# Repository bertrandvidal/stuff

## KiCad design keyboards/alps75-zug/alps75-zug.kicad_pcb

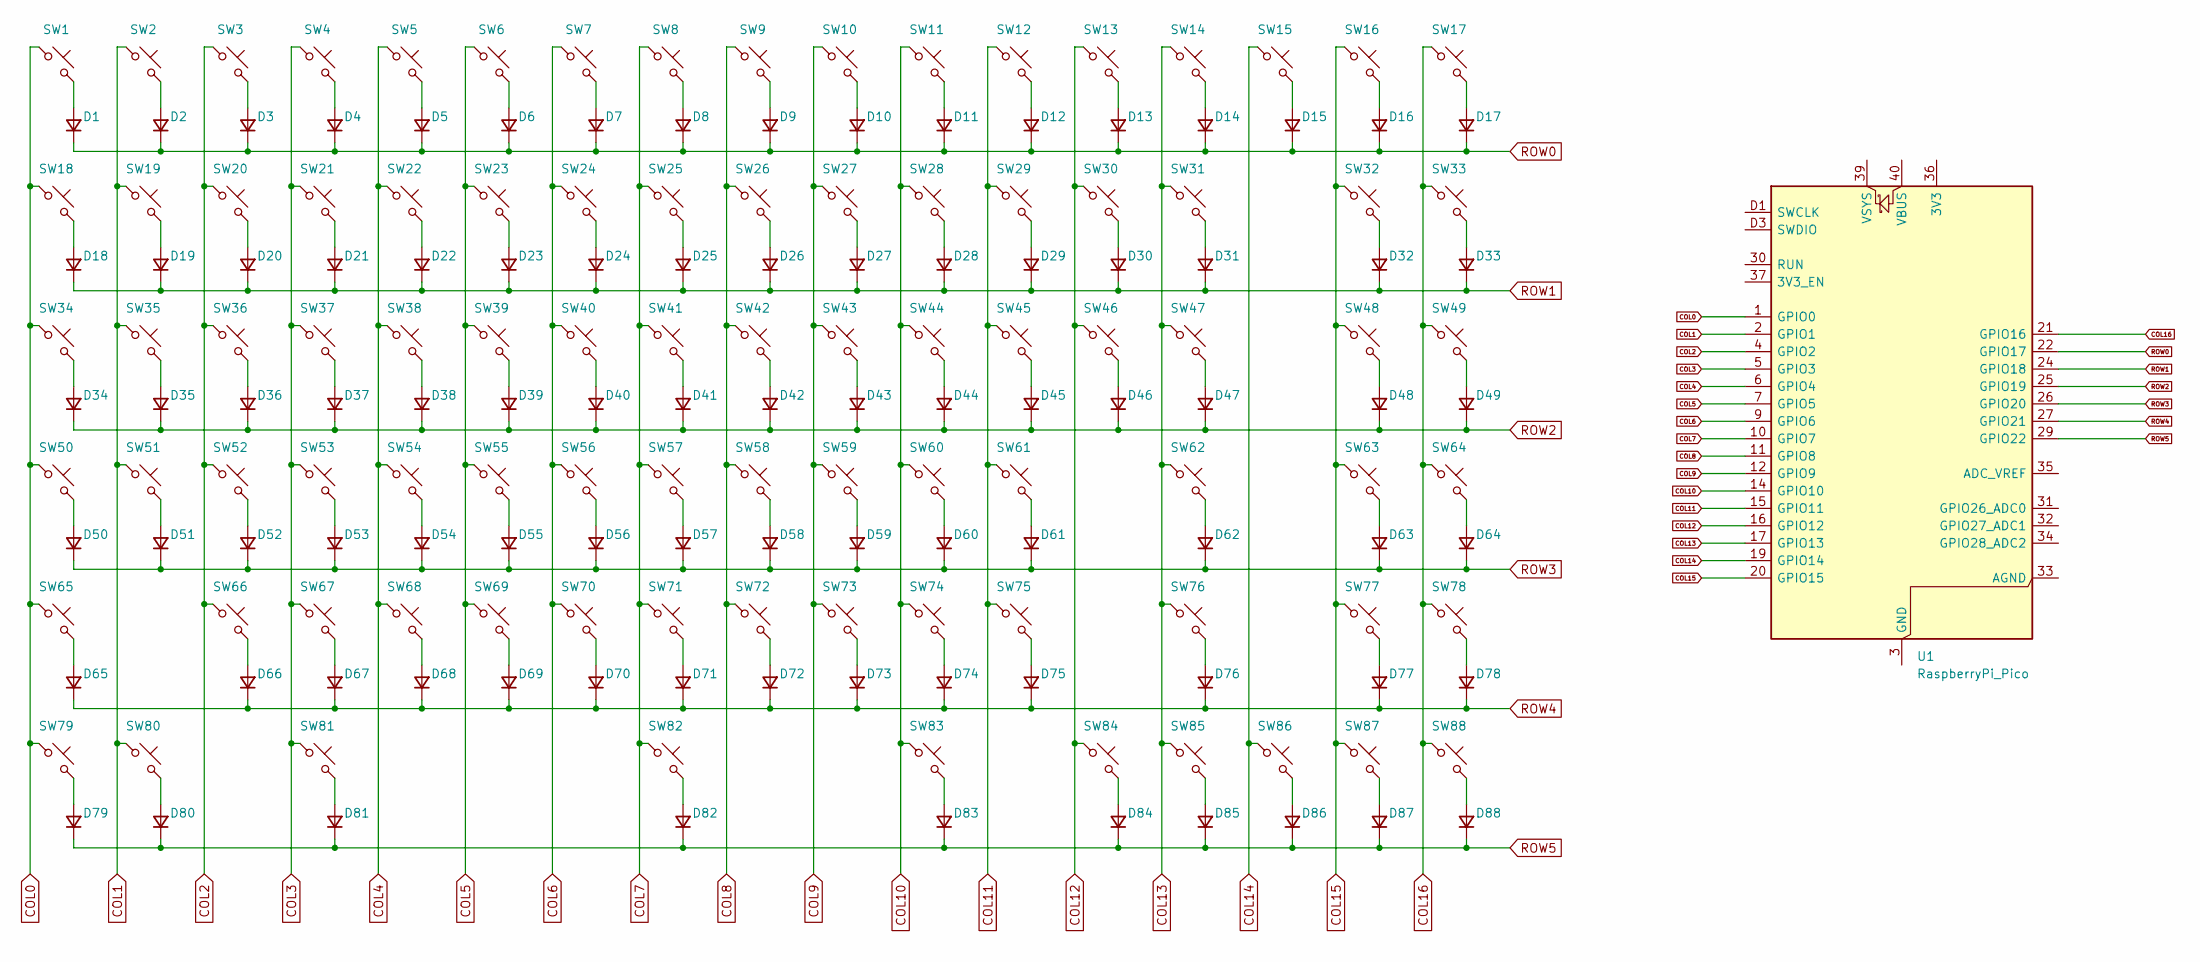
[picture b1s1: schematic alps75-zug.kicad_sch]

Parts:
D1, D2, D3, D4, D5, D6, D7, D8, D9, D10, D11, D12, D13, D14, D15, D16, D17, D18, D19, D20, D21, D22, D23, D24, D25, D26, D27, D28, D29, D30, D31, D32, D33, D34, D35, D36, D37, D38, D39, D40, D41, D42, D43, D44, D45, D46, D47, D48, D49, D50, D51, D52, D53, D54, D55, D56, D57, D58, D59, D60, D61, D62, D63, D64, D65, D66, D67, D68, D69, D70, D71, D72, D73, D74, D75, D76, D77, D78, D79, D80, D81, D82, D83, D84, D85, D86, D87, D88: 1N4148WL; D_SOD-123F; LCSC C108804
SW1, SW2, SW3, SW4, SW5, SW6, SW7, SW8, SW9, SW10, SW11, SW12, SW13, SW14, SW15, SW16, SW17, SW18, SW19, SW20, SW21, SW22, SW23, SW24, SW25, SW26, SW27, SW28, SW29, SW30, SW32, SW33, SW35, SW36, SW37, SW38, SW39, SW40, SW41, SW42, SW43, SW44, SW45, SW46, SW48, SW49, SW51, SW52, SW53, SW54, SW55, SW56, SW57, SW58, SW59, SW60, SW61, SW63, SW64, SW66, SW67, SW68, SW69, SW70, SW71, SW72, SW73, SW74, SW75, SW77, SW78, SW84, SW85, SW86, SW87, SW88: SW_Push; SW_Alps_Matias_1.00u
SW31: SW_Push; SW_Alps_Matias_2.00u
SW34, SW47, SW79, SW81: SW_Push; SW_Alps_Matias_1.50u
SW50: SW_Push; SW_Alps_Matias_1.75u
SW62, SW65: SW_Push; SW_Alps_Matias_2.25u
SW76: SW_Push; SW_Alps_Matias_2.75u
SW80, SW83: SW_Push; SW_Alps_Matias_1.25u
SW82: SW_Push; SW_Alps_Matias_6.50u
U1: RaspberryPi_Pico; RaspberryPi_Pico_SMD_HandSolder

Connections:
COL0: SW1.1, SW18.1, SW34.1, SW50.1, SW65.1, SW79.1, U1.1 (GPIO0)
COL1: SW2.1, SW19.1, SW35.1, SW51.1, SW80.1, U1.2 (GPIO1)
COL2: SW3.1, SW20.1, SW36.1, SW52.1, SW66.1, U1.4 (GPIO2)
COL3: SW4.1, SW21.1, SW37.1, SW53.1, SW67.1, SW81.1, U1.5 (GPIO3)
COL4: SW5.1, SW22.1, SW38.1, SW54.1, SW68.1, U1.6 (GPIO4)
COL5: SW6.1, SW23.1, SW39.1, SW55.1, SW69.1, U1.7 (GPIO5)
COL6: SW7.1, SW24.1, SW40.1, SW56.1, SW70.1, U1.9 (GPIO6)
COL7: SW8.1, SW25.1, SW41.1, SW57.1, SW71.1, SW82.1, U1.10 (GPIO7)
COL8: SW9.1, SW26.1, SW42.1, SW58.1, SW72.1, U1.11 (GPIO8)
COL9: SW10.1, SW27.1, SW43.1, SW59.1, SW73.1, U1.12 (GPIO9)
COL10: SW11.1, SW28.1, SW44.1, SW60.1, SW74.1, SW83.1, U1.14 (GPIO10)
COL11: SW12.1, SW29.1, SW45.1, SW61.1, SW75.1, U1.15 (GPIO11)
COL12: SW13.1, SW30.1, SW46.1, SW84.1, U1.16 (GPIO12)
COL13: SW14.1, SW31.1, SW47.1, SW62.1, SW76.1, SW85.1, U1.17 (GPIO13)
COL14: SW15.1, SW86.1, U1.19 (GPIO14)
COL15: SW16.1, SW32.1, SW48.1, SW63.1, SW77.1, SW87.1, U1.20 (GPIO15)
COL16: SW17.1, SW33.1, SW49.1, SW64.1, SW78.1, SW88.1, U1.21 (GPIO16)
unnamed: D1.2 (A), SW1.2
unnamed: D2.2 (A), SW2.2
unnamed: D3.2 (A), SW3.2
unnamed: D4.2 (A), SW4.2
unnamed: D5.2 (A), SW5.2
unnamed: D6.2 (A), SW6.2
unnamed: D7.2 (A), SW7.2
unnamed: D8.2 (A), SW8.2
unnamed: D9.2 (A), SW9.2
unnamed: D10.2 (A), SW10.2
unnamed: D11.2 (A), SW11.2
unnamed: D12.2 (A), SW12.2
unnamed: D13.2 (A), SW13.2
unnamed: D14.2 (A), SW14.2
unnamed: D15.2 (A), SW15.2
unnamed: D16.2 (A), SW16.2
unnamed: D17.2 (A), SW17.2
unnamed: D18.2 (A), SW18.2
unnamed: D19.2 (A), SW19.2
unnamed: D20.2 (A), SW20.2
unnamed: D21.2 (A), SW21.2
unnamed: D22.2 (A), SW22.2
unnamed: D23.2 (A), SW23.2
unnamed: D24.2 (A), SW24.2
unnamed: D25.2 (A), SW25.2
unnamed: D26.2 (A), SW26.2
unnamed: D27.2 (A), SW27.2
unnamed: D28.2 (A), SW28.2
unnamed: D29.2 (A), SW29.2
unnamed: D30.2 (A), SW30.2
unnamed: D31.2 (A), SW31.2
unnamed: D32.2 (A), SW32.2
unnamed: D33.2 (A), SW33.2
unnamed: D34.2 (A), SW34.2
unnamed: D35.2 (A), SW35.2
unnamed: D36.2 (A), SW36.2
unnamed: D37.2 (A), SW37.2
unnamed: D38.2 (A), SW38.2
unnamed: D39.2 (A), SW39.2
unnamed: D40.2 (A), SW40.2
unnamed: D41.2 (A), SW41.2
unnamed: D42.2 (A), SW42.2
unnamed: D43.2 (A), SW43.2
unnamed: D44.2 (A), SW44.2
unnamed: D45.2 (A), SW45.2
unnamed: D46.2 (A), SW46.2
unnamed: D47.2 (A), SW47.2
unnamed: D48.2 (A), SW48.2
unnamed: D49.2 (A), SW49.2
unnamed: D50.2 (A), SW50.2
unnamed: D51.2 (A), SW51.2
unnamed: D52.2 (A), SW52.2
unnamed: D53.2 (A), SW53.2
unnamed: D54.2 (A), SW54.2
unnamed: D55.2 (A), SW55.2
unnamed: D56.2 (A), SW56.2
unnamed: D57.2 (A), SW57.2
unnamed: D58.2 (A), SW58.2
unnamed: D59.2 (A), SW59.2
unnamed: D60.2 (A), SW60.2
unnamed: D61.2 (A), SW61.2
unnamed: D62.2 (A), SW62.2
unnamed: D63.2 (A), SW63.2
unnamed: D64.2 (A), SW64.2
unnamed: D65.2 (A), SW65.2
unnamed: D66.2 (A), SW66.2
unnamed: D67.2 (A), SW67.2
unnamed: D68.2 (A), SW68.2
unnamed: D69.2 (A), SW69.2
unnamed: D70.2 (A), SW70.2
unnamed: D71.2 (A), SW71.2
unnamed: D72.2 (A), SW72.2
unnamed: D73.2 (A), SW73.2
unnamed: D74.2 (A), SW74.2
unnamed: D75.2 (A), SW75.2
unnamed: D76.2 (A), SW76.2
unnamed: D77.2 (A), SW77.2
unnamed: D78.2 (A), SW78.2
unnamed: D79.2 (A), SW79.2
unnamed: D80.2 (A), SW80.2
unnamed: D81.2 (A), SW81.2
unnamed: D82.2 (A), SW82.2
unnamed: D83.2 (A), SW83.2
unnamed: D84.2 (A), SW84.2
unnamed: D85.2 (A), SW85.2
unnamed: D86.2 (A), SW86.2
unnamed: D87.2 (A), SW87.2
unnamed: D88.2 (A), SW88.2
unnamed: U1.3 (GND), U1.8 (GND), U1.13 (GND), U1.18 (GND), U1.23 (GND), U1.28 (GND), U1.38 (GND), U1.D2 (GND)
ROW0: D1.1 (K), D2.1 (K), D3.1 (K), D4.1 (K), D5.1 (K), D6.1 (K), D7.1 (K), D8.1 (K), D9.1 (K), D10.1 (K), D11.1 (K), D12.1 (K), D13.1 (K), D14.1 (K), D15.1 (K), D16.1 (K), D17.1 (K), U1.22 (GPIO17)
ROW1: D18.1 (K), D19.1 (K), D20.1 (K), D21.1 (K), D22.1 (K), D23.1 (K), D24.1 (K), D25.1 (K), D26.1 (K), D27.1 (K), D28.1 (K), D29.1 (K), D30.1 (K), D31.1 (K), D32.1 (K), D33.1 (K), U1.24 (GPIO18)
ROW2: D34.1 (K), D35.1 (K), D36.1 (K), D37.1 (K), D38.1 (K), D39.1 (K), D40.1 (K), D41.1 (K), D42.1 (K), D43.1 (K), D44.1 (K), D45.1 (K), D46.1 (K), D47.1 (K), D48.1 (K), D49.1 (K), U1.25 (GPIO19)
ROW3: D50.1 (K), D51.1 (K), D52.1 (K), D53.1 (K), D54.1 (K), D55.1 (K), D56.1 (K), D57.1 (K), D58.1 (K), D59.1 (K), D60.1 (K), D61.1 (K), D62.1 (K), D63.1 (K), D64.1 (K), U1.26 (GPIO20)
ROW4: D65.1 (K), D66.1 (K), D67.1 (K), D68.1 (K), D69.1 (K), D70.1 (K), D71.1 (K), D72.1 (K), D73.1 (K), D74.1 (K), D75.1 (K), D76.1 (K), D77.1 (K), D78.1 (K), U1.27 (GPIO21)
ROW5: D79.1 (K), D80.1 (K), D81.1 (K), D82.1 (K), D83.1 (K), D84.1 (K), D85.1 (K), D86.1 (K), D87.1 (K), D88.1 (K), U1.29 (GPIO22)

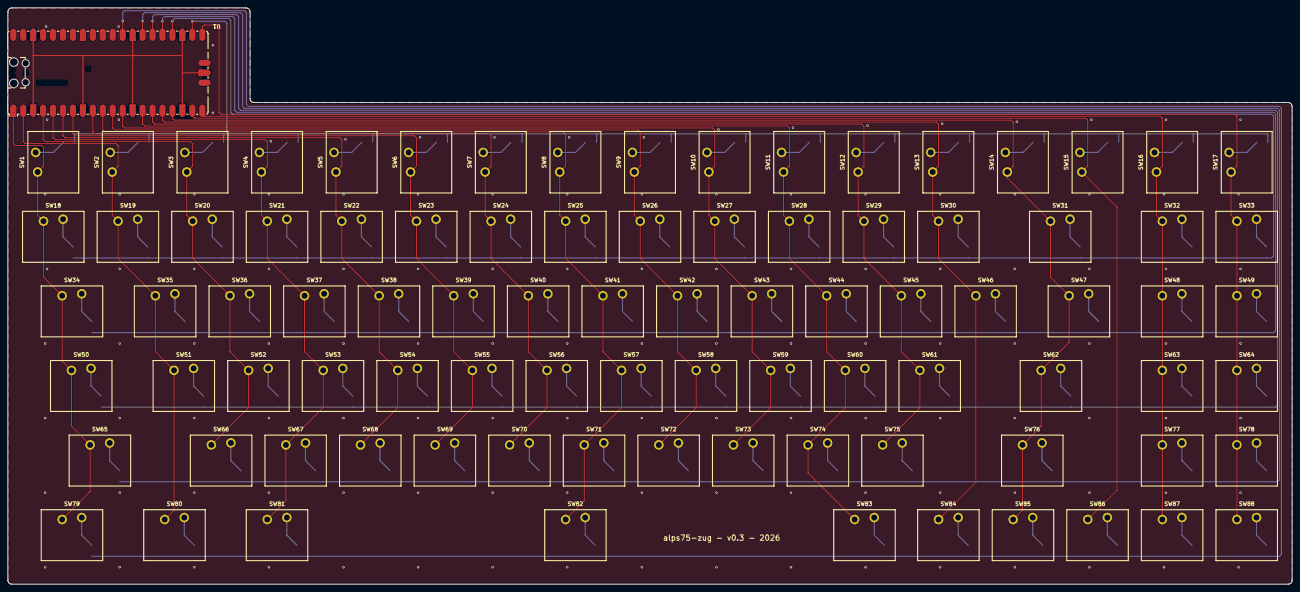
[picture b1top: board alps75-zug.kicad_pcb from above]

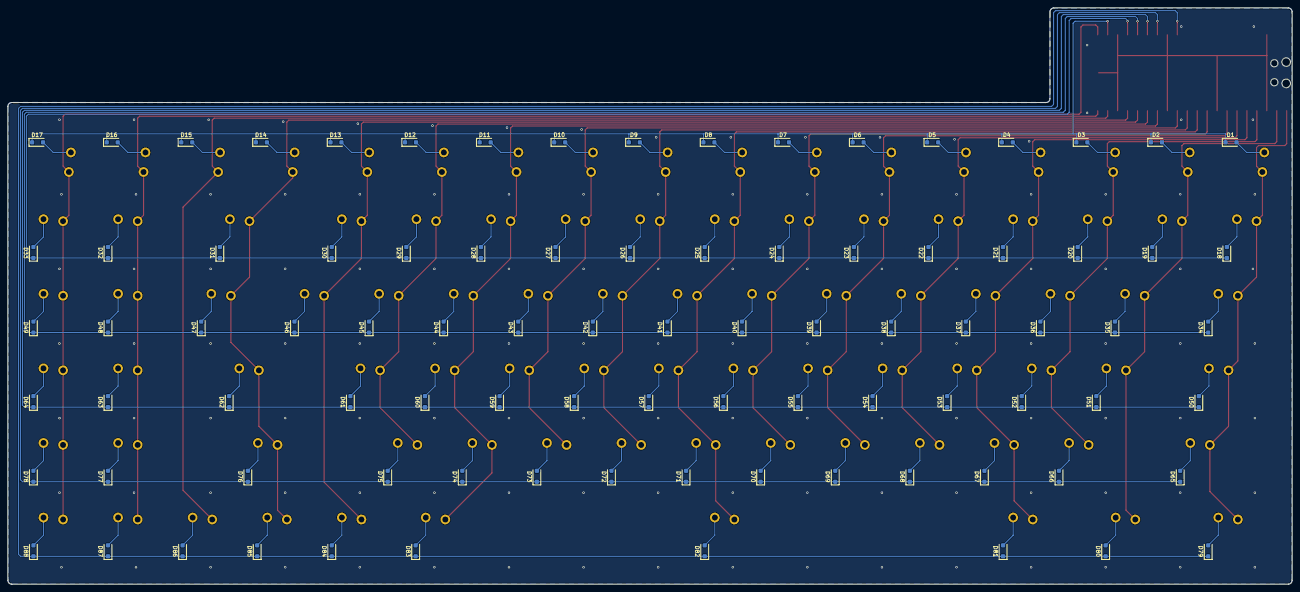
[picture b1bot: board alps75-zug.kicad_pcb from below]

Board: 2 copper layers, 328.0 x 147.2 mm, 177 parts (88 on the bottom side), 112 nets.

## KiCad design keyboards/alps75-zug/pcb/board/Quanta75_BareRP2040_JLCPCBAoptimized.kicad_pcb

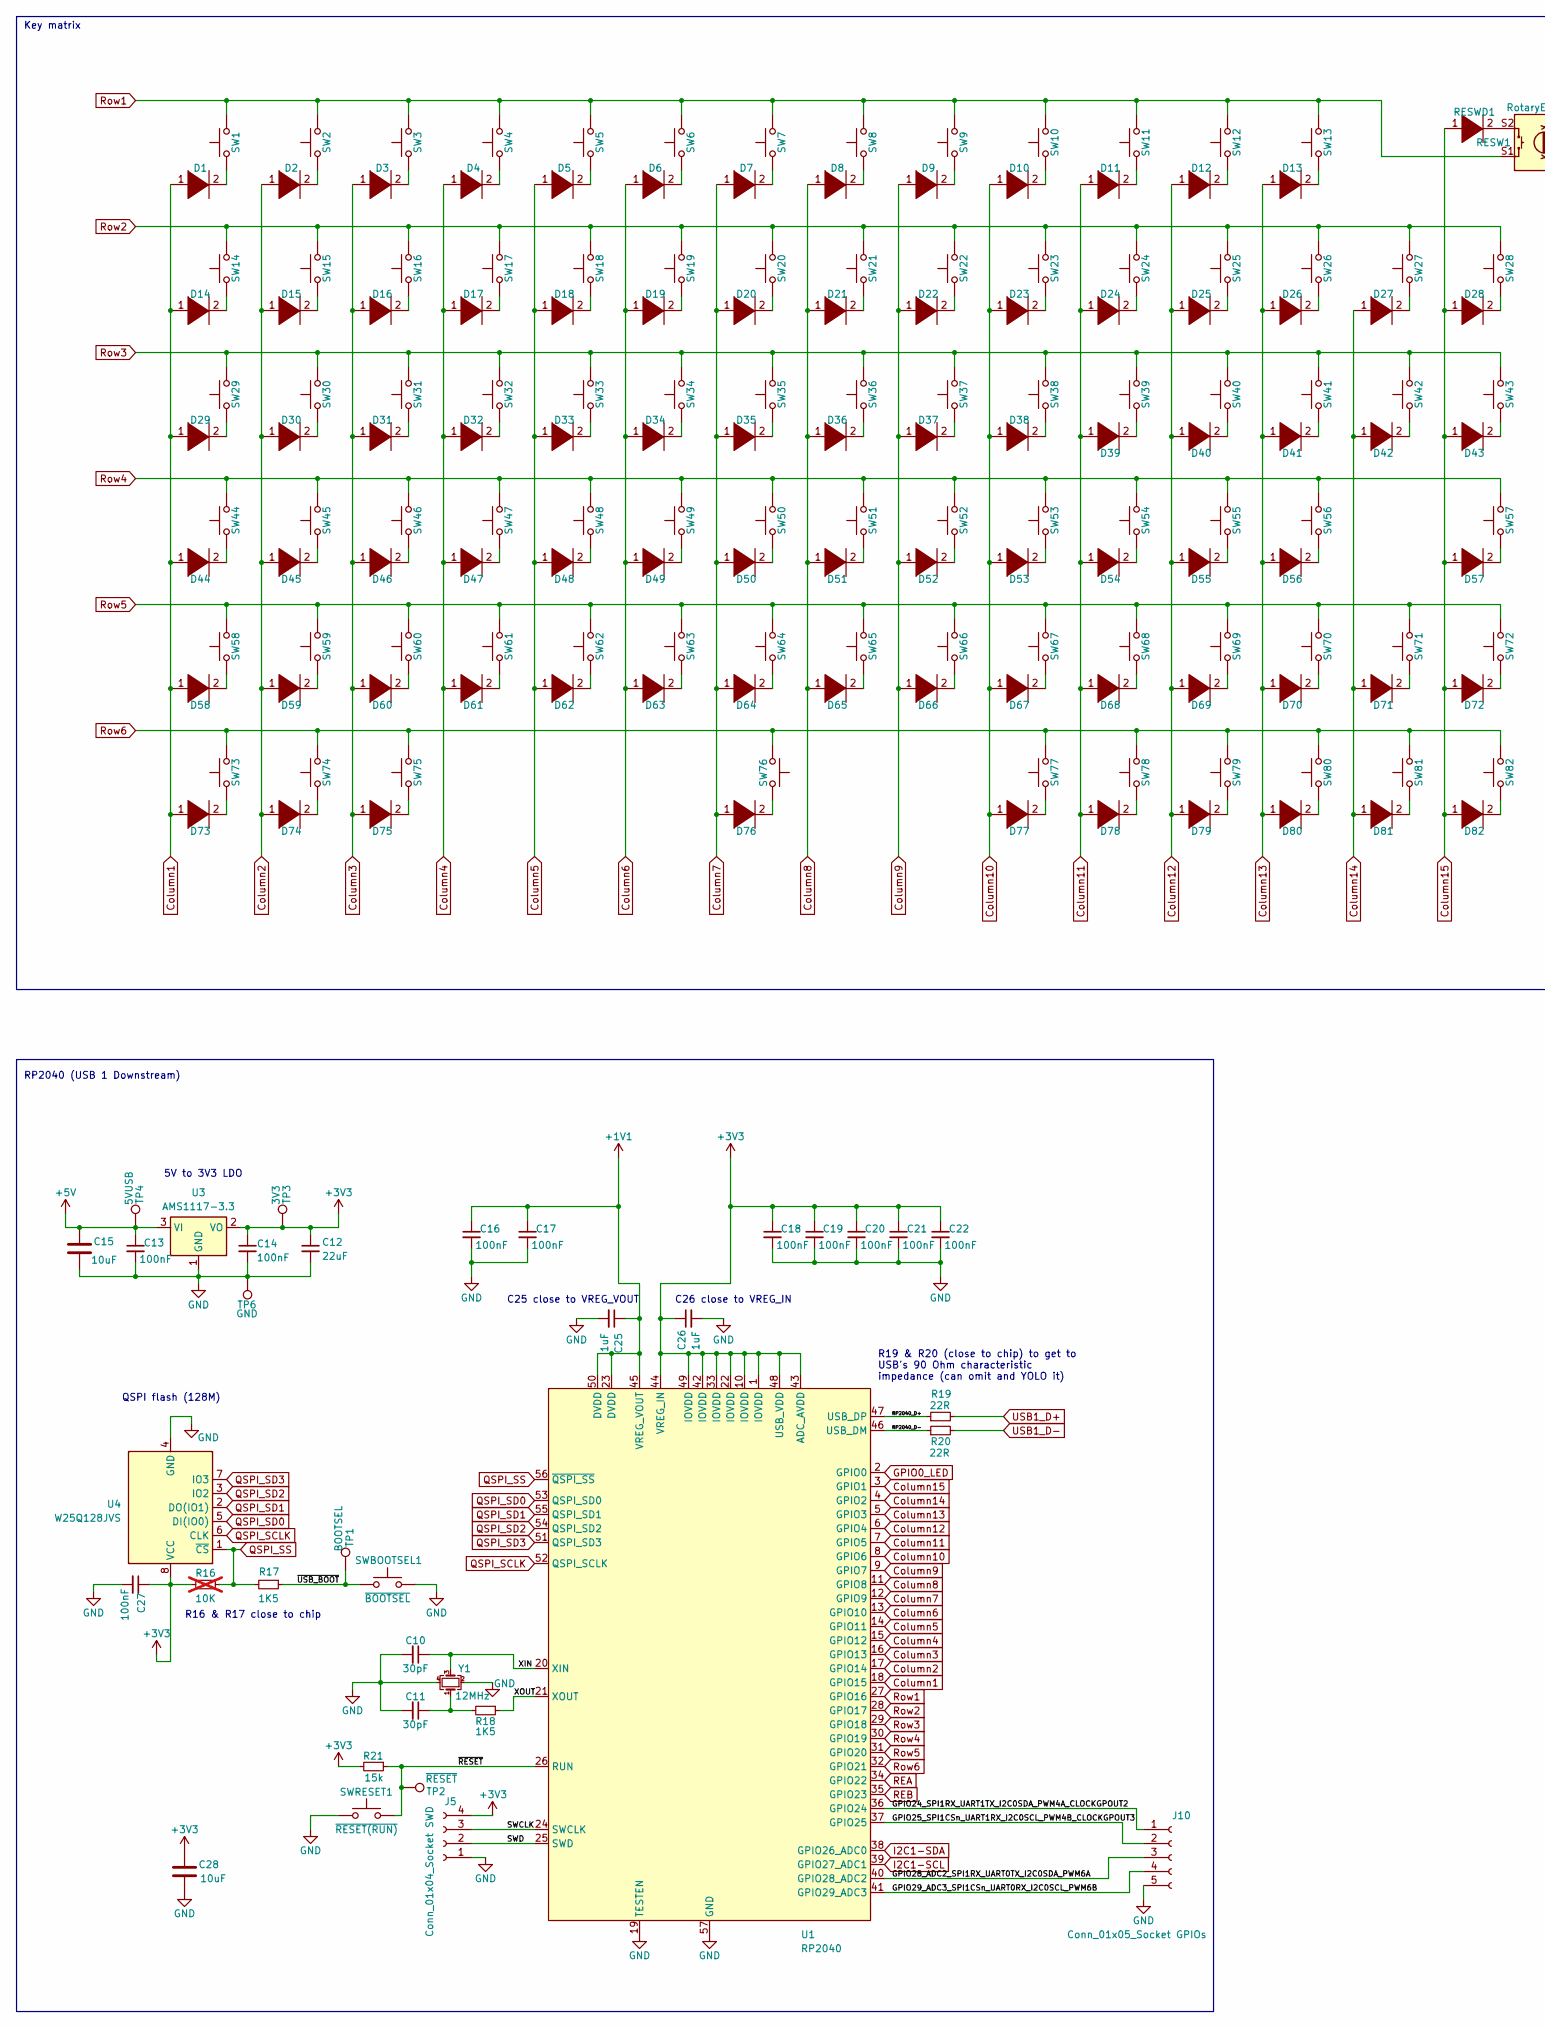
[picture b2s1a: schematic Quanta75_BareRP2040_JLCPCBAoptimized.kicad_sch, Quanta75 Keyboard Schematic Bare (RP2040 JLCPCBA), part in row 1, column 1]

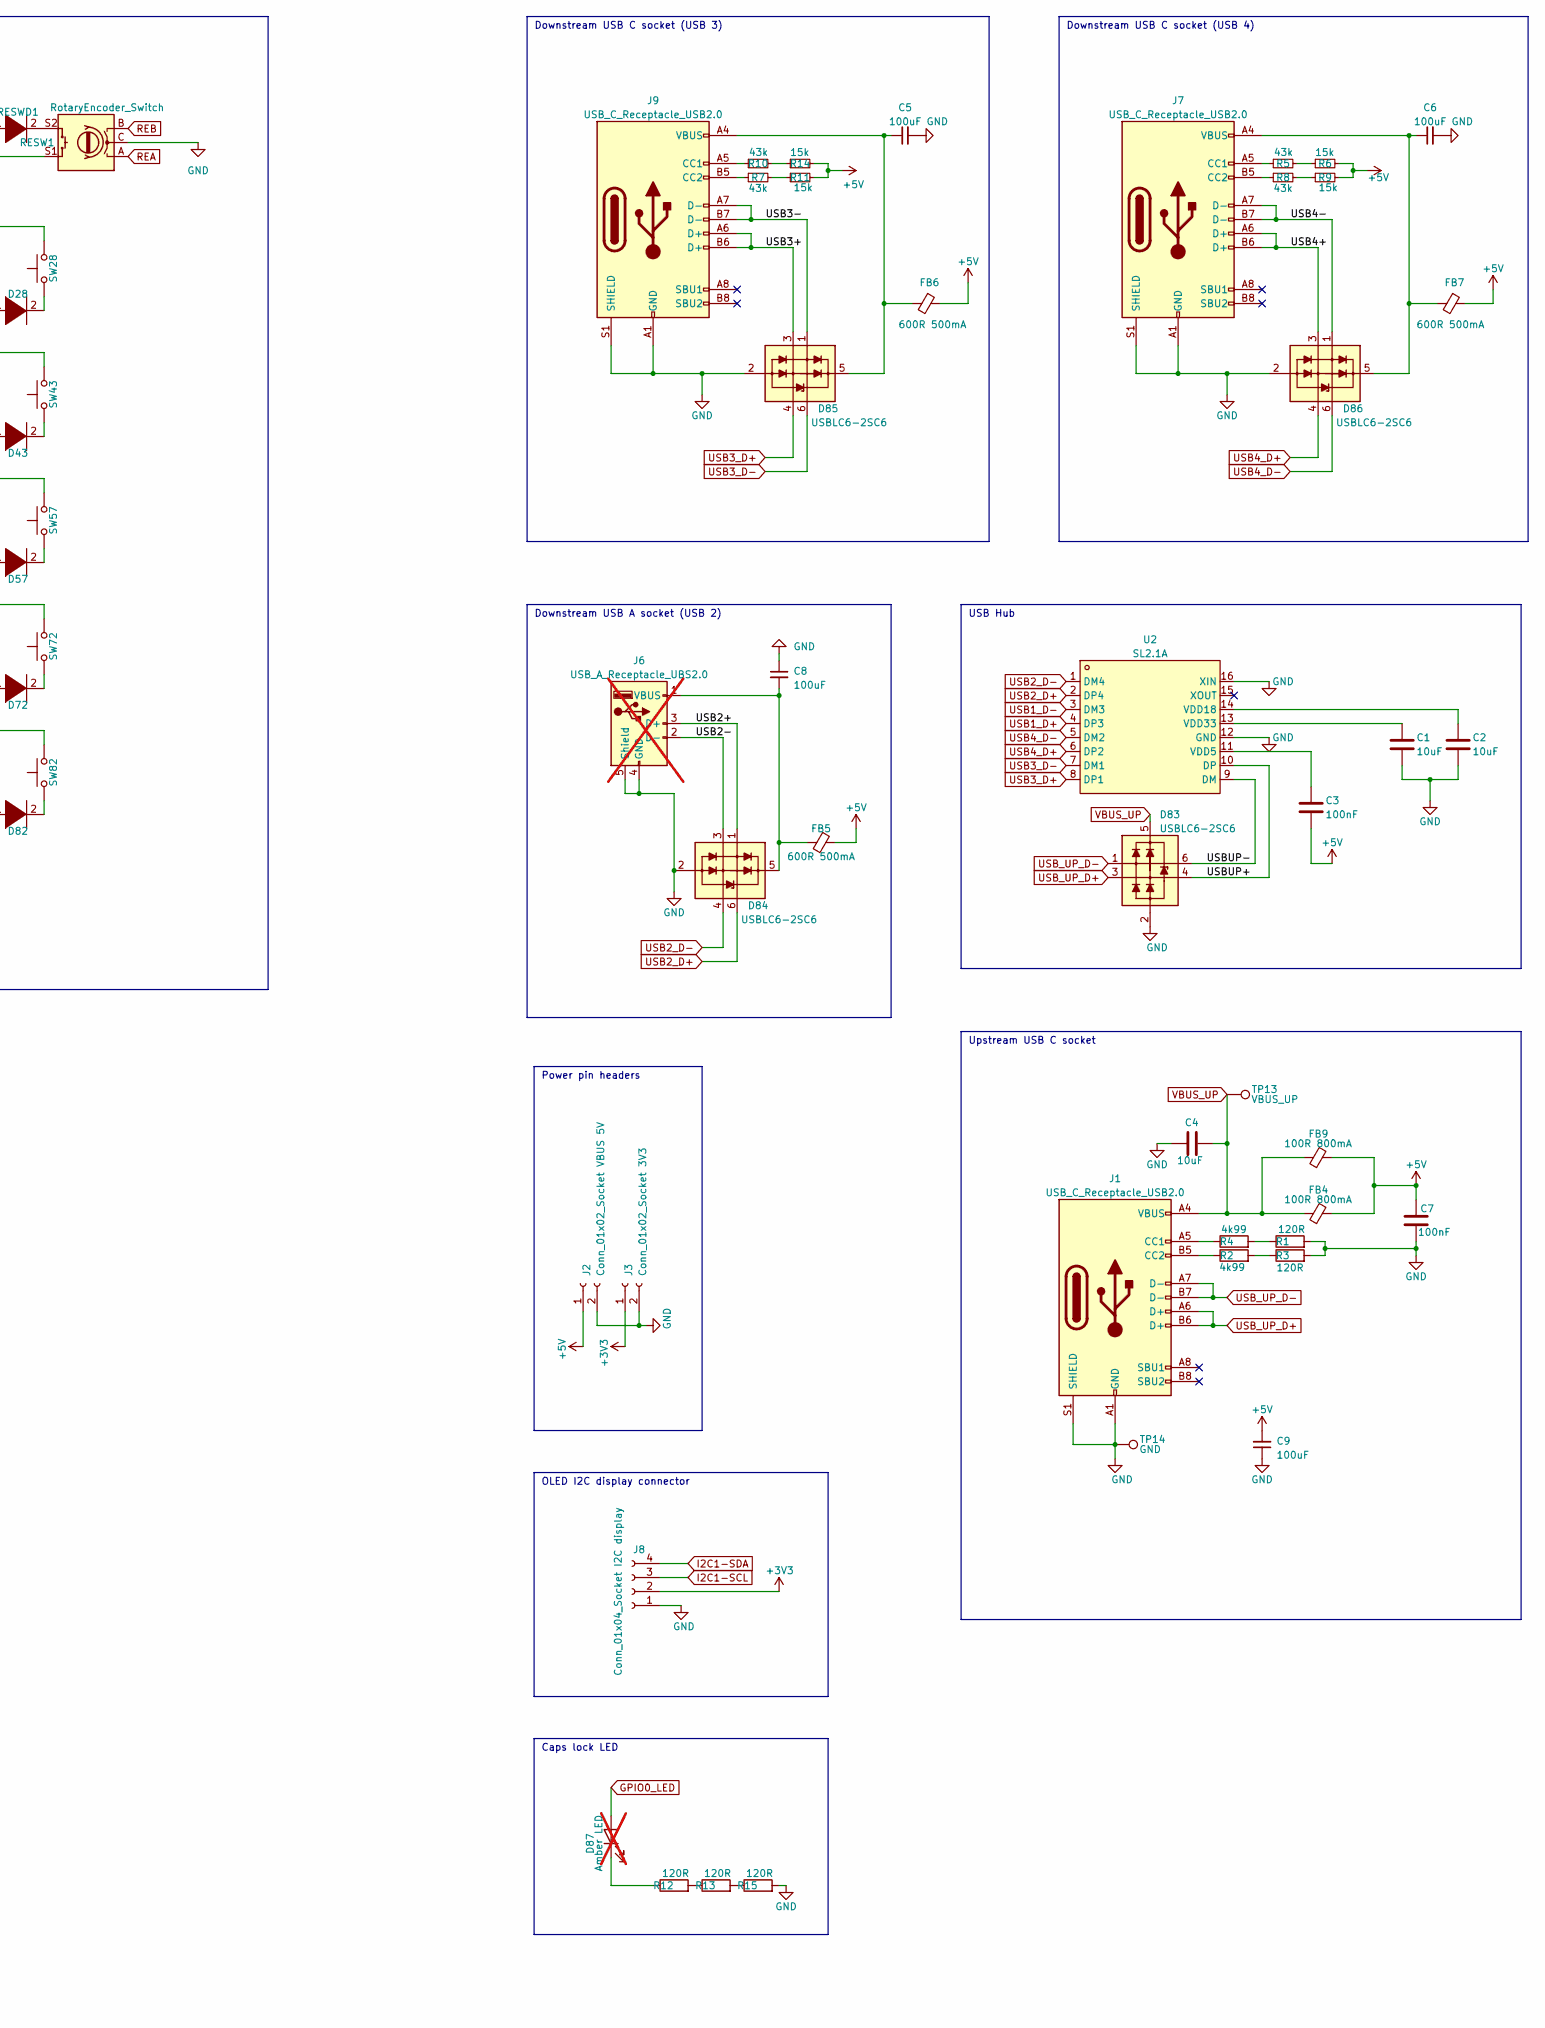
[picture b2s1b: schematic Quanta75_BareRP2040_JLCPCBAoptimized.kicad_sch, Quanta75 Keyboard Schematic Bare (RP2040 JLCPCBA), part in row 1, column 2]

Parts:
C1, C2, C4, C15, C28: 10uF; C_0603_1608Metric_Pad1.08x0.95mm_HandSolder; JLCPCB C96446
C3, C7, C13, C14, C16, C17, C18, C19, C20, C21, C22: 100nF; C_0603_1608Metric_Pad1.08x0.95mm_HandSolder; JLCPCB C14663
C5, C6, C8, C9: 100uF; C_1206_3216Metric_Pad1.33x1.80mm_HandSolder; JLCPCB C15008
C10, C11: 30pF; C_0603_1608Metric_Pad1.08x0.95mm_HandSolder; JLCPCB C1658
C12: 22uF; C_0805_2012Metric_Pad1.18x1.45mm_HandSolder; JLCPCB C45783
C25, C26: 1uF; C_0402_1005Metric_Pad0.74x0.62mm_HandSolder; JLCPCB C52923
C27: 100nF; R_0603_1608Metric_Pad0.98x0.95mm_HandSolder; JLCPCB C14663
D1: DIODE; D_SOD-123; JLCPCB C81598
D2, D3, D4, D5, D6, D7, D8, D9, D10, D11, D12, D13, D14, D15, D16, D17, D18, D19, D20, D21, D22, D23, D24, D25, D26, D27, D28, D29, D30, D31, D32, D33, D34, D35, D36, D37, D38, D39, D40, D41, D42, D43, D44, D45, D46, D47, D48, D49, D50, D51, D52, D53, D54, D55, D56, D57, D58, D59, D60, D61, D62, D63, D64, D65, D66, D67, D68, D69, D70, D71, D72, D73, D74, D75, D76, D77, D78, D79, D80, D81, D82: DIODE; D_SOD-123
D83, D84, D85, D86: USBLC6-2SC6; SOT-23-6_Handsoldering
D87: Amber LED; LED_D5.0mm_Clear; not fitted
FB4, FB9: 100R 800mA; Ferrite_0805_2012Metric_Pad1.05x1.20mm_BigPads; JLCPCB part number C1015
FB5: 600R 500mA; Ferrite_0805_2012Metric; JLCPCB part number C1017
FB6, FB7: 600R 500mA; Ferrite_0805_2012Metric; JLCPCB part numb C1017
J1, J7, J9: USB_C_Receptacle_USB2.0; USB-C-SMD_G-SWITCH_GT-USB-7010EN; JLCPCB C3001293
J2: Conn_01x02_Socket VBUS 5V; PinHeader_1x02_P2.54mm_Vertical
J3: Conn_01x02_Socket 3V3; PinHeader_1x02_P2.54mm_Vertical
J5: Conn_01x04_Socket SWD; PinHeader_1x04_P2.54mm_Vertical
J6: USB_A_Receptacle_UBS2.0; USB-A-TH_KH-AF180ZJ-13.7; JLCPCB C2833345; not fitted
J8: Conn_01x04_Socket I2C display; PinHeader_1x04_P2.54mm_Vertical
J10: Conn_01x05_Socket GPIOs; PinHeader_1x05_P2.54mm_Vertical
R1, R3, R12, R13, R15: 120R; R_0603_1608Metric_Pad0.98x0.95mm_HandSolder; JLCPCB C22787
R2, R4: 4k99; R_0603_1608Metric_Pad0.98x0.95mm_HandSolder; JLCPCB C23046
R5, R7, R8, R10: 43k; R_0603_1608Metric_Pad0.98x0.95mm_HandSolder; JLCPCB C23172
R6, R9, R11, R14, R21: 15k; R_0603_1608Metric_Pad0.98x0.95mm_HandSolder; JLCPCB C22809
R16: 10K; R_0603_1608Metric_Pad0.98x0.95mm_HandSolder; not fitted
R17, R18: 1K5; R_0603_1608Metric_Pad0.98x0.95mm_HandSolder; JLCPCB C22843
R19, R20: 22R; R_0402_1005Metric_Pad0.72x0.64mm_HandSolder; JLCPCB C25092
RESW1: RotaryEncoder_Switch; RotaryEncoder_both_AlpsEC11E-S_BournsPEC12R-3-S
RESWD1: DIODE; D_SOD-123
SW1, SW2, SW3, SW4, SW5, SW6, SW7, SW8, SW9, SW10, SW11, SW12, SW13, SW14, SW15, SW16, SW17, SW18, SW19, SW20, SW21, SW22, SW23, SW24, SW25, SW26, SW28, SW30, SW31, SW32, SW33, SW34, SW35, SW36, SW37, SW38, SW39, SW40, SW41, SW43, SW45, SW46, SW47, SW48, SW49, SW50, SW51, SW52, SW53, SW54, SW55, SW56, SW57, SW59, SW60, SW61, SW62, SW63, SW64, SW65, SW66, SW67, SW68, SW69, SW71, SW72, SW77, SW78, SW79, SW80, SW81, SW82: SW_Push; Alps-Solderable-1U
SW27: SW_Push; Alps-Solderable-2U
SW29: SW_Push; Alps-Solderable-1.5U
SW42: SW_Push; SW_Cherry_MX_ISOEnter_PCB
SW44, SW70: SW_Push; Alps-Solderable-1.75U
SW58, SW73, SW74, SW75: SW_Push; Alps-Solderable-1.25U
SW76: SW_Push; Alps-Solderable-6.25U
SWBOOTSEL1: ~{BOOTSEL}; SW_Push_1P1T_XKB_TS-1187A; JLCPCB C318884
SWRESET1: ~{RESET(RUN)}; SW_Push_1P1T_XKB_TS-1187A; JLCPCB C318884
TP1: BOOTSEL; TestPoint_Pad_D1.5mm
TP2: ~{RESET}; TestPoint_Pad_D1.5mm
TP3: 3V3; TestPoint_Pad_D1.5mm
TP4: 5VUSB; TestPoint_Pad_D1.5mm
TP6, TP14: GND; TestPoint_Pad_D1.5mm
TP13: VBUS_UP; TestPoint_Pad_D1.5mm
U1: RP2040; QFN-56-1EP_7x7mm_P0.4mm_EP3.2x3.2mm_ThermalVias; LCSC Part C2040
U2: SL2.1A; SOP-16_L10.0-W3.9-P1.27-LS6.0-BL; LCSC Part C192893
U3: AMS1117-3.3; SOT-223-3_TabPin2; JLCPCB C6186
U4: W25Q128JVS; SOIC-8_5.23x5.23mm_P1.27mm; JLCPCB C97521
Y1: 12MHz; Crystal_SMD_3225-4Pin_3.2x2.5mm_HandSoldering; JLCPCB C9002

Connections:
+1V1: C16.1, C17.1, C25.1, U1.23 (DVDD), U1.45 (VREG_VOUT), U1.50 (DVDD)
+3V3: C12.1, C14.1, C18.1, C19.1, C20.1, C21.1, C22.1, C26.1, C27.1, C28.2, J3.1, J5.4, J8.2, R16.2, R21.2, TP3.1, U1.1 (IOVDD), U1.10 (IOVDD), U1.22 (IOVDD), U1.33 (IOVDD), U1.42 (IOVDD), U1.43 (ADC_AVDD), U1.44 (VREG_IN), U1.48 (USB_VDD), U1.49 (IOVDD), U3.2 (VO), U4.8 (VCC)
+5V: C3.2, C7.2, C9.2, C13.1, C15.2, FB4.2, FB5.1, FB6.1, FB7.1, FB9.2, J2.1, R6.2, R9.2, R11.2, R14.2, TP4.1, U3.3 (VI)
/GPIO24_SPI1RX_UART1TX_I2C0SDA_PWM4A_CLOCKGPOUT2: J10.1, U1.36 (GPIO24)
/GPIO25_SPI1CSn_UART1RX_I2C0SCL_PWM4B_CLOCKGPOUT3: J10.2, U1.37 (GPIO25)
/GPIO28_ADC2_SPI1RX_UART0TX_I2C0SDA_PWM6A: J10.3, U1.40 (GPIO28_ADC2)
/GPIO29_ADC3_SPI1CSn_UART0RX_I2C0SCL_PWM6B: J10.4, U1.41 (GPIO29_ADC3)
/RP2040_D+: R19.1, U1.47 (USB_DP)
/RP2040_D-: R20.1, U1.46 (USB_DM)
/SWCLK: J5.3, U1.24 (SWCLK)
/SWD: J5.2, U1.25 (SWD)
/USB2+: D84.1 (L1), J6.3 (D+)
/USB2-: D84.3 (L2), J6.2 (D-)
/USB3+: D85.3 (L2), J9.A6 (D+), J9.B6 (D+)
/USB3-: D85.1 (L1), J9.A7 (D-), J9.B7 (D-)
/USB4+: D86.3 (L2), J7.A6 (D+), J7.B6 (D+)
/USB4-: D86.1 (L1), J7.A7 (D-), J7.B7 (D-)
/USBUP+: D83.4 (L2), U2.10 (DP)
/USBUP-: D83.6 (L1), U2.9 (DM)
/XIN: C10.1, U1.20 (XIN), Y1.3
/XOUT: R18.1, U1.21 (XOUT)
/~RESET: R21.1, SWRESET1.2, TP2.1, U1.26 (RUN)
/~USB_BOOT: R17.1, SWBOOTSEL1.1, TP1.1
Column1: D1.1 (K), D14.1 (K), D29.1 (K), D44.1 (K), D58.1 (K), D73.1 (K), U1.18 (GPIO15)
Column2: D2.1 (K), D15.1 (K), D30.1 (K), D45.1 (K), D59.1 (K), D74.1 (K), U1.17 (GPIO14)
Column3: D3.1 (K), D16.1 (K), D31.1 (K), D46.1 (K), D60.1 (K), D75.1 (K), U1.16 (GPIO13)
Column4: D4.1 (K), D17.1 (K), D32.1 (K), D47.1 (K), D61.1 (K), U1.15 (GPIO12)
Column5: D5.1 (K), D18.1 (K), D33.1 (K), D48.1 (K), D62.1 (K), U1.14 (GPIO11)
Column6: D6.1 (K), D19.1 (K), D34.1 (K), D49.1 (K), D63.1 (K), U1.13 (GPIO10)
Column7: D7.1 (K), D20.1 (K), D35.1 (K), D50.1 (K), D64.1 (K), D76.1 (K), U1.12 (GPIO9)
Column8: D8.1 (K), D21.1 (K), D36.1 (K), D51.1 (K), D65.1 (K), U1.11 (GPIO8)
Column9: D9.1 (K), D22.1 (K), D37.1 (K), D52.1 (K), D66.1 (K), U1.9 (GPIO7)
Column10: D10.1 (K), D23.1 (K), D38.1 (K), D53.1 (K), D67.1 (K), D77.1 (K), U1.8 (GPIO6)
Column11: D11.1 (K), D24.1 (K), D39.1 (K), D54.1 (K), D68.1 (K), D78.1 (K), U1.7 (GPIO5)
Column12: D12.1 (K), D25.1 (K), D40.1 (K), D55.1 (K), D69.1 (K), D79.1 (K), U1.6 (GPIO4)
Column13: D13.1 (K), D26.1 (K), D41.1 (K), D56.1 (K), D70.1 (K), D80.1 (K), U1.5 (GPIO3)
Column14: D27.1 (K), D42.1 (K), D71.1 (K), D81.1 (K), U1.4 (GPIO2)
Column15: D28.1 (K), D43.1 (K), D57.1 (K), D72.1 (K), D82.1 (K), RESWD1.1 (K), U1.3 (GPIO1)
GND: C1.2, C2.2, C4.1, C5.2, C6.2, C7.1, C8.1, C9.1, C10.2, C11.2, C12.2, C13.2, C14.2, C15.1, C16.2, C17.2, C18.2, C19.2, C20.2, C21.2, C22.2, C25.2, C26.2, C27.2, C28.1, D83.2 (VN), D84.2 (VN), D85.2 (VN), D86.2 (VN), J1.2, J1.A1 (GND), J1.A12 (GND), J1.B1 (GND), J1.B12 (GND), J1.S1 (SHIELD), J2.2, J3.2, J5.1, J6.4 (GND), J6.5 (Shield), J7.2, J7.A1 (GND), J7.A12 (GND), J7.B1 (GND), J7.B12 (GND), J7.S1 (SHIELD), J8.1, J9.2, J9.A1 (GND), J9.A12 (GND), J9.B1 (GND), J9.B12 (GND), J9.S1 (SHIELD), J10.5, R1.2, R3.2, R15.2, RESW1.C, RESW1.SH, SWBOOTSEL1.2, SWRESET1.1, TP6.1, TP14.1, U1.19 (TESTEN), U1.57 (GND), U2.12 (GND), U2.16 (XIN), U3.1 (GND), U4.4 (GND), Y1.2, Y1.4; also elsewhere on the board
GPIO0_LED: D87.2 (A), U1.2 (GPIO0)
I2C1-SCL: J8.3, U1.39 (GPIO27_ADC1)
I2C1-SDA: J8.4, U1.38 (GPIO26_ADC0)
unnamed: C11.1, R18.2, Y1.1
unnamed: D1.2 (A), SW1.1
unnamed: D2.2 (A), SW2.1
unnamed: D3.2 (A), SW3.1
unnamed: D4.2 (A), SW4.1
unnamed: D5.2 (A), SW5.1
unnamed: D6.2 (A), SW6.1
unnamed: D7.2 (A), SW7.1
unnamed: D8.2 (A), SW8.1
unnamed: D9.2 (A), SW9.1
unnamed: D10.2 (A), SW10.1
unnamed: D11.2 (A), SW11.1
unnamed: D12.2 (A), SW12.1
unnamed: D13.2 (A), SW13.1
unnamed: D14.2 (A), SW14.1
unnamed: D15.2 (A), SW15.1
unnamed: D16.2 (A), SW16.1
unnamed: D17.2 (A), SW17.1
unnamed: D18.2 (A), SW18.1
unnamed: D19.2 (A), SW19.1
unnamed: D20.2 (A), SW20.1
unnamed: D21.2 (A), SW21.1
unnamed: D22.2 (A), SW22.1
unnamed: D23.2 (A), SW23.1
unnamed: D24.2 (A), SW24.1
unnamed: D25.2 (A), SW25.1
unnamed: D26.2 (A), SW26.1
unnamed: D27.2 (A), SW27.1
unnamed: D28.2 (A), SW28.1
unnamed: D29.2 (A), SW29.1
unnamed: D30.2 (A), SW30.1
unnamed: D31.2 (A), SW31.1
unnamed: D32.2 (A), SW32.1
unnamed: D33.2 (A), SW33.1
unnamed: D34.2 (A), SW34.1
unnamed: D35.2 (A), SW35.1
unnamed: D36.2 (A), SW36.1
unnamed: D37.2 (A), SW37.1
unnamed: D38.2 (A), SW38.1
unnamed: D39.2 (A), SW39.1
unnamed: D40.2 (A), SW40.1
unnamed: D41.2 (A), SW41.1
unnamed: D42.2 (A), SW42.1
unnamed: D43.2 (A), SW43.1
unnamed: D44.2 (A), SW44.1
unnamed: D45.2 (A), SW45.1
unnamed: D46.2 (A), SW46.1
unnamed: D47.2 (A), SW47.1
unnamed: D48.2 (A), SW48.1
unnamed: D49.2 (A), SW49.1
unnamed: D50.2 (A), SW50.1
unnamed: D51.2 (A), SW51.1
unnamed: D52.2 (A), SW52.1
unnamed: D53.2 (A), SW53.1
unnamed: D54.2 (A), SW54.1
unnamed: D55.2 (A), SW55.1
unnamed: D56.2 (A), SW56.1
unnamed: D57.2 (A), SW57.1
unnamed: D58.2 (A), SW58.1
unnamed: D59.2 (A), SW59.1
unnamed: D60.2 (A), SW60.1
unnamed: D61.2 (A), SW61.1
unnamed: D62.2 (A), SW62.1
unnamed: D63.2 (A), SW63.1
unnamed: D64.2 (A), SW64.1
unnamed: D65.2 (A), SW65.1
unnamed: D66.2 (A), SW66.1
unnamed: D67.2 (A), SW67.1
unnamed: D68.2 (A), SW68.1
unnamed: D69.2 (A), SW69.1
unnamed: D70.2 (A), SW70.1
unnamed: D71.2 (A), SW71.1
unnamed: D72.2 (A), SW72.1
unnamed: D73.2 (A), SW73.1
unnamed: D74.2 (A), SW74.1
unnamed: D75.2 (A), SW75.1
unnamed: D76.2 (A), SW76.2
unnamed: D77.2 (A), SW77.1
unnamed: D78.2 (A), SW78.1
unnamed: D79.2 (A), SW79.1
unnamed: D80.2 (A), SW80.1
unnamed: D81.2 (A), SW81.1
unnamed: D82.2 (A), SW82.1
unnamed: C8.2, D84.5 (VP), FB5.2, J6.1 (VBUS)
unnamed: C5.1, D85.5 (VP), FB6.2, J9.A4 (VBUS), J9.A9 (VBUS), J9.B4 (VBUS), J9.B9 (VBUS)
unnamed: C6.1, D86.5 (VP), FB7.2, J7.A4 (VBUS), J7.A9 (VBUS), J7.B4 (VBUS), J7.B9 (VBUS)
unnamed: D87.1 (K), R12.1
unnamed: J1.A5 (CC1), R4.1
unnamed: J1.B5 (CC2), R2.1
unnamed: J7.A5 (CC1), R5.1
unnamed: J7.B5 (CC2), R8.1
unnamed: J9.A5 (CC1), R10.1
unnamed: J9.B5 (CC2), R7.1
unnamed: R1.1, R4.2
unnamed: R2.2, R3.1
unnamed: R5.2, R6.1
unnamed: R8.2, R9.1
unnamed: R10.2, R14.1
unnamed: R7.2, R11.1
unnamed: R12.2, R13.1
unnamed: R13.2, R15.1
unnamed: RESW1.S2, RESWD1.2 (A)
unnamed: C3.1, U2.11 (VDD5)
unnamed: C2.1, U2.14 (VDD18)
unnamed: C1.1, U2.13 (VDD33)
QSPI_SCLK: U1.52 (QSPI_SCLK), U4.6 (CLK)
QSPI_SD0: U1.53 (QSPI_SD0), U4.5 (DI(IO0))
QSPI_SD1: U1.55 (QSPI_SD1), U4.2 (DO(IO1))
QSPI_SD2: U1.54 (QSPI_SD2), U4.3 (IO2)
QSPI_SD3: U1.51 (QSPI_SD3), U4.7 (IO3)
QSPI_SS: R16.1, R17.2, U1.56 (~QSPI_SS), U4.1 (~CS)
REA: RESW1.A, U1.34 (GPIO22)
REB: RESW1.B, U1.35 (GPIO23)
Row1: RESW1.S1, SW1.2, SW2.2, SW3.2, SW4.2, SW5.2, SW6.2, SW7.2, SW8.2, SW9.2, SW10.2, SW11.2, SW12.2, SW13.2, U1.27 (GPIO16)
Row2: SW14.2, SW15.2, SW16.2, SW17.2, SW18.2, SW19.2, SW20.2, SW21.2, SW22.2, SW23.2, SW24.2, SW25.2, SW26.2, SW27.2, SW28.2, U1.28 (GPIO17)
Row3: SW29.2, SW30.2, SW31.2, SW32.2, SW33.2, SW34.2, SW35.2, SW36.2, SW37.2, SW38.2, SW39.2, SW40.2, SW41.2, SW42.2, SW43.2, U1.29 (GPIO18)
Row4: SW44.2, SW45.2, SW46.2, SW47.2, SW48.2, SW49.2, SW50.2, SW51.2, SW52.2, SW53.2, SW54.2, SW55.2, SW56.2, SW57.2, U1.30 (GPIO19)
Row5: SW58.2, SW59.2, SW60.2, SW61.2, SW62.2, SW63.2, SW64.2, SW65.2, SW66.2, SW67.2, SW68.2, SW69.2, SW70.2, SW71.2, SW72.2, U1.31 (GPIO20)
Row6: SW73.2, SW74.2, SW75.2, SW76.1, SW77.2, SW78.2, SW79.2, SW80.2, SW81.2, SW82.2, U1.32 (GPIO21)
USB1_D+: R19.2, U2.4 (DP3)
USB1_D-: R20.2, U2.3 (DM3)
USB2_D+: D84.6 (L1), U2.2 (DP4)
USB2_D-: D84.4 (L2), U2.1 (DM4)
USB3_D+: D85.4 (L2), U2.8 (DP1)
USB3_D-: D85.6 (L1), U2.7 (DM1)
USB4_D+: D86.4 (L2), U2.6 (DP2)
USB4_D-: D86.6 (L1), U2.5 (DM2)
USB_UP_D+: D83.3 (L2), J1.A6 (D+), J1.B6 (D+)
USB_UP_D-: D83.1 (L1), J1.A7 (D-), J1.B7 (D-)
VBUS_UP: C4.2, D83.5 (VP), FB4.1, FB9.1, J1.A4 (VBUS), J1.A9 (VBUS), J1.B4 (VBUS), J1.B9 (VBUS), TP13.1

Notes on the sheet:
Downstream USB C socket (USB 3)
OLED I2C display connector
Downstream USB C socket (USB 4)
R16 & R17 close to chip
QSPI flash (128M)
5V to 3V3 LDO
Key matrix
C25 close to VREG_VOUT
Upstream USB C socket
Downstream USB A socket (USB 2)
RP2040 (USB 1 Downstream)
R19 & R20 (close to chip) to get to USB's 90 Ohm characteristic impedance (can omit and YOLO it)
USB Hub
C26 close to VREG_IN
Power pin headers
Caps lock LED
